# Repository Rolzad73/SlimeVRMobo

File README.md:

# SlimeVRMobo

PCB to mount components for SlimeVR trackers

https://docs.slimevr.dev/

- minimal holes and traces
- main components used: 
  - ESP8266 WeMos D1 Mini microcontroller
  -  TP4056 battery charger
  -  MPU-6050 gyro/accelerometer (GY-521 board)

KiCad 6.0 compatibility

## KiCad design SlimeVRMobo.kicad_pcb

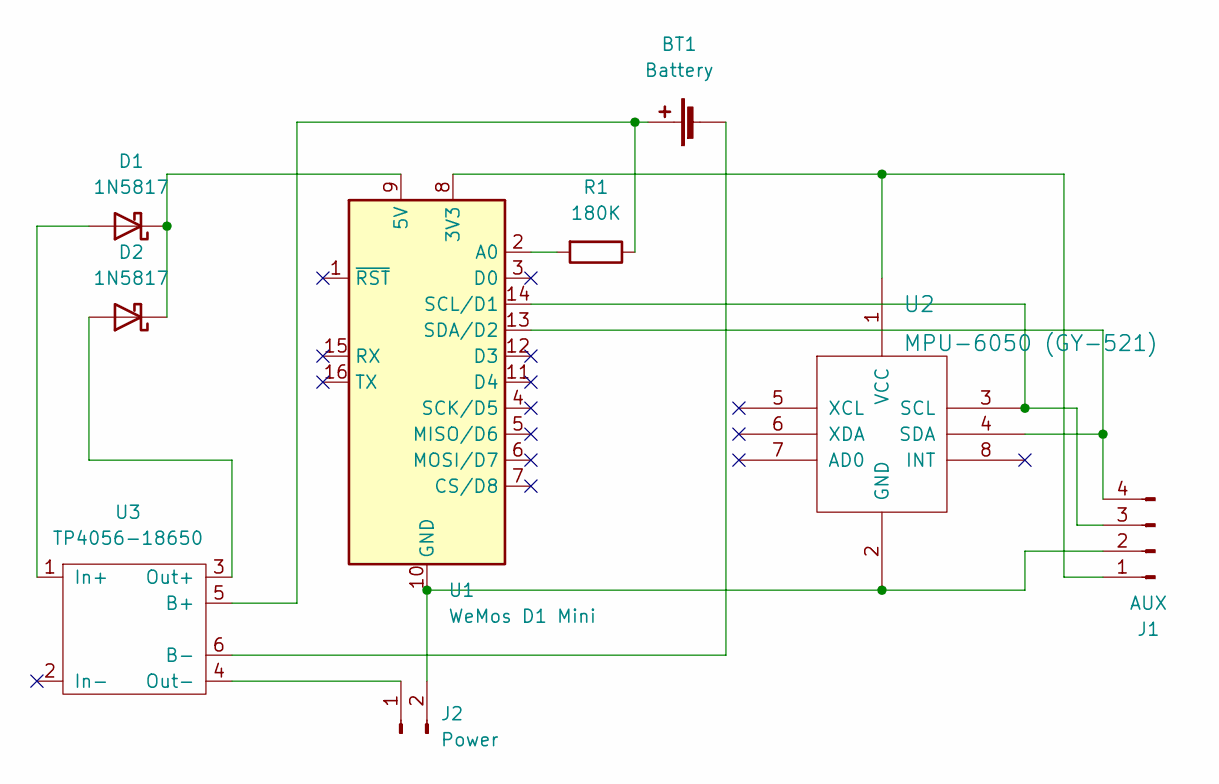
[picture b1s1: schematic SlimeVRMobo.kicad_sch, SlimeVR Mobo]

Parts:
BT1: Battery
D1, D2: 1N5817; D_DO-41_SOD81_P10.16mm_Horizontal
J1: AUX; JST_XH_B4B-XH-A_1x04_P2.50mm_Vertical
J2: Power; PinHeader_1x02_P2.54mm_Vertical
R1: 180K; R_Axial_DIN0207_L6.3mm_D2.5mm_P7.62mm_Horizontal
U1: WeMos D1 Mini; WEMOS_D1_mini_light
U2: MPU-6050 (GY-521); GY-521
U3: TP4056-18650

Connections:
unnamed: BT1.1 (+), R1.1, U3.5 (B+)
unnamed: BT1.2 (-), U3.6 (B-)
unnamed: D1.1 (K), D2.1 (K), U1.9 (5V)
unnamed: D1.2 (A), U3.1 (In+)
unnamed: D2.2 (A), U3.3 (Out+)
unnamed: J1.1, U1.8 (3V3), U2.1 (VCC)
unnamed: J2.1, U3.4 (Out-)
unnamed: J1.2, J2.2, U1.10 (GND), U2.2 (GND)
unnamed: R1.2, U1.2 (A0)
unnamed: J1.4, U1.13 (SDA/D2), U2.4 (SDA)
unnamed: J1.3, U1.14 (SCL/D1), U2.3 (SCL)

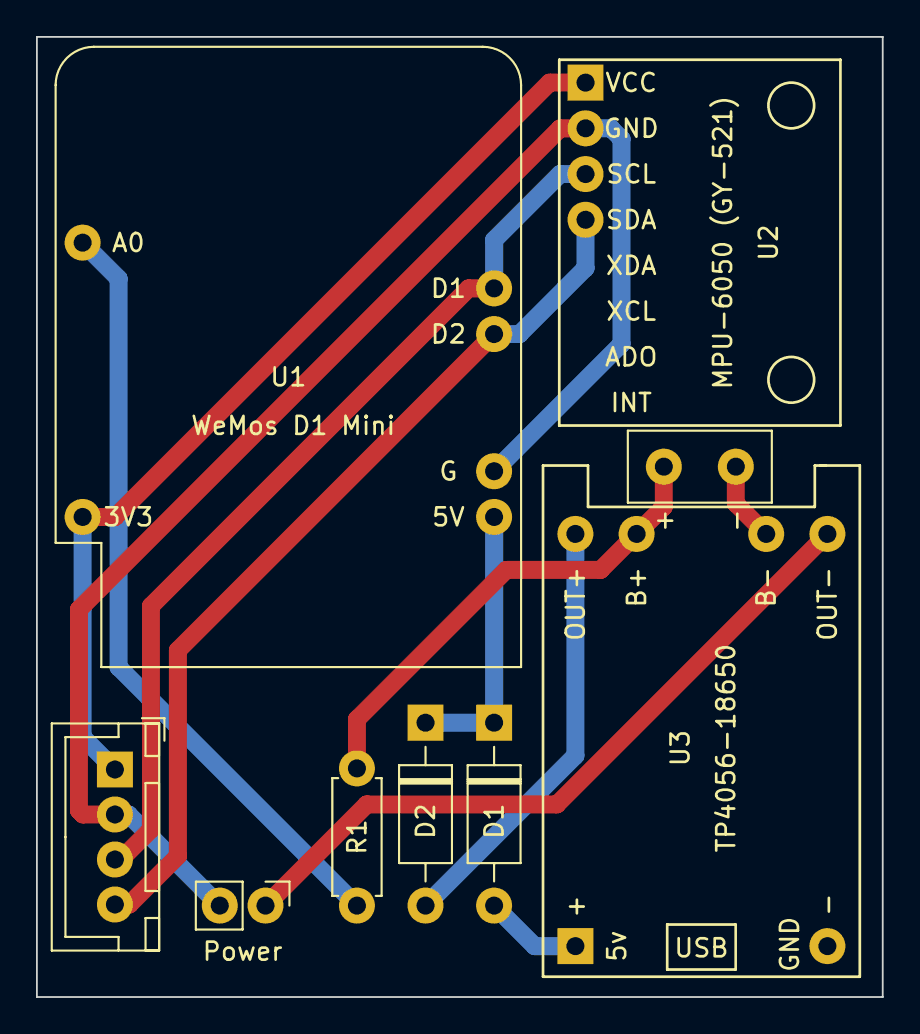
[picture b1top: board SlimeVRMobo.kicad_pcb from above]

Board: 2 copper layers, 47.0 x 53.3 mm, 9 parts (0 on the bottom side), 11 nets.

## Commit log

2022-03-05 - init commit
